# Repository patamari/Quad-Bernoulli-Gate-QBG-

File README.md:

This is a dual 4U adaptation of Mutable Instruments Branches. Hardware is cc-by-sa-3.0.

The only change component wise I had to make was to lower the values of the resistors for the -5V reference from 10K to 3.3K.

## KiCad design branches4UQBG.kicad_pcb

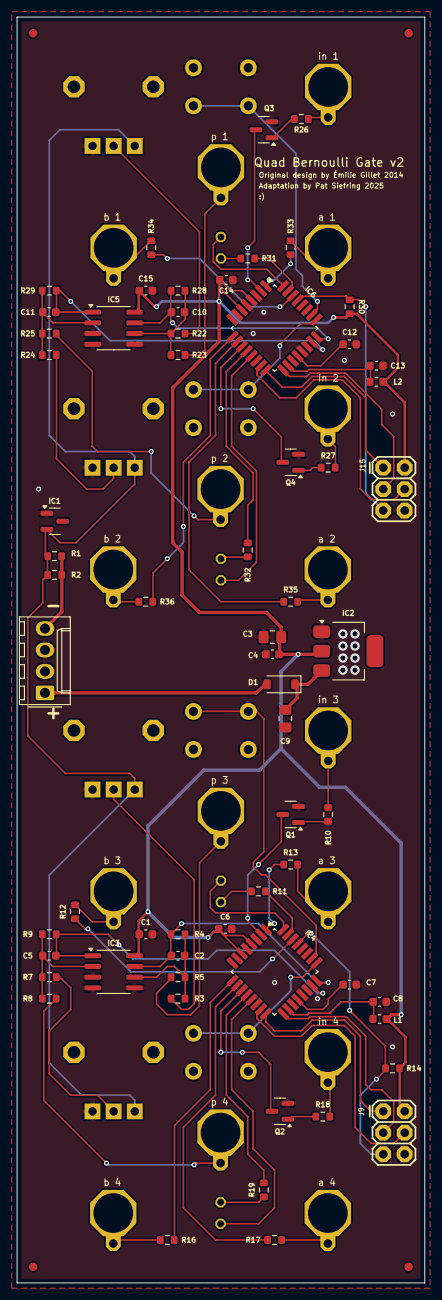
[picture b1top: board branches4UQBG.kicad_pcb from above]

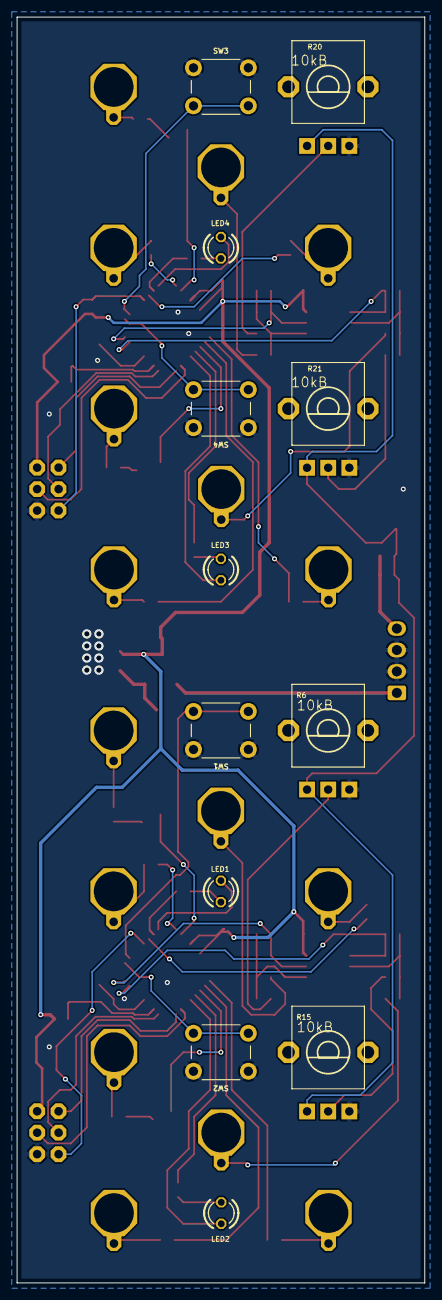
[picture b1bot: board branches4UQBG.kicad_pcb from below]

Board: 2 copper layers, 48.3 x 149.9 mm, 78 parts (12 on the bottom side), 61 nets.

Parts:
C1, C4, C6, C7, C8, C12, C13, C14, C15: 100n; C_0603_1608Metric
C2, C5, C10, C11: 1n; C_0603_1608Metric
C3, C9: 10uF; C_0805_2012Metric_Pad1.18x1.45mm_HandSolder
D1: 1N5819HW; D_SOD-123
F1, F2, F3, F4: FIDUCIAL1X2; FIDUCIAL-1X2
IC1: LM4040 5.0V; SOT-23
IC2: LM1117-5.0; SOT-223
IC3, IC5: MCP6002; SOIC-8_3.9x4.9mm_P1.27mm
IC4, IC6: ATMEGA88PA-AU; TQFP-32_7x7mm_P0.8mm
J9: 2X3
J15: AVR_SPI_PRG_6PTH; 2X3
L1: L_0603_1608Metric
L2: WE-CBF_0603; L_0603_1608Metric
LED1, LED2, LED3, LED4: WP937EGW; LED3MM
Q1, Q2, Q3, Q4: MMBT3904; SOT-23
R1, R2: 3.3K; R_0603_1608Metric
R3, R4, R5, R7, R8, R9, R10, R18, R22, R23, R24, R25, R26, R27, R28, R29: 100k; R_0603_1608Metric
R6, R15, R20, R21: 10kB; ALPS_POT_VERTICAL_PS
R11, R19, R31, R32: 220; R_0603_1608Metric
R12, R13, R16, R17, R33, R34, R35, R36: 1.0k; R_0603_1608Metric
R14, R30: 10k; R_0603_1608Metric
SW1, SW2: SW_PUSH_6mm_H4.3mm
SW3, SW4: TAC_SWITCHPTH; SW_PUSH_6mm_H4.3mm

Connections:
+5V: C1.1, C3.1, C4.1, C6.1, C14.1, C15.1, IC2.2, IC3.8, IC4.4, IC4.6, IC5.8, IC6.4 (VCC@1), IC6.6 (VCC@2), J9.2, J15.2, L1.1, L2.1, R14.2, R30.2
/AREF: C12.1, IC6.20 (AREF)
/IN1: IC6.2 (PD4(XCK/T0)), Q3.3
/IN2: IC6.11 (PD7(AIN1)), Q4.3
/MISO: IC6.16 (PB4(MISO)), J15.1
/MOSI: IC6.15 (PB3(MOSI/OC2)), J15.4
/OUT1_A: IC6.1 (PD3(INT1)), R33.1
/OUT1_B: IC6.30 (PD0(RXD)), R34.1
/OUT2_A: IC6.10 (PD6(AIN0)), R35.1
/OUT2_B: IC6.9 (PD5(T1)), R36.1
/P1_CV: C10.2, IC5.7 (OUT), IC6.24 (PC1(ADC1)), R28.2
/P2_CV: C11.2, IC5.1 (OUT), IC6.23 (PC0(ADC0)), R29.2
/RESET: IC6.29 (PC6(/RESET)), J15.5, R30.1
/SCK: IC6.17 (PB5(SCK)), J15.3
/SW1: IC6.26 (PC3(ADC3)), SW3.2
/SW2: IC6.25 (PC2(ADC2)), SW4.2
AREF: C7.1, IC4.20
GND: C1.2, C3.2, C4.2, C6.2, C7.2, C8.2, C9.2, C12.2, C13.2, C14.2, C15.2, IC1.1, IC2.1, IC3.3, IC3.4, IC3.5, IC4.3, IC4.5, IC4.21, IC5.3 (+IN), IC5.4, IC5.5 (+IN), IC6.3 (GND@1), IC6.5 (AGND), IC6.21 (GND@2), J9.6, J15.6, Q1.2, Q2.2, Q3.2, Q4.2, R6.P$1, R15.P$1, R20.P$1 (E), R21.P$1 (E), SW1.1, SW2.1, SW3.1, SW4.1
IN1: IC4.2, Q1.3
IN2: IC4.11, Q2.3
MISO: IC4.16, J9.1
MOSI: IC4.15, J9.4
unnamed: Q1.1, R10.1
unnamed: Q2.1, R18.1
unnamed: C5.1, IC3.2, R7.2, R8.2, R9.1
unnamed: R7.1, R15.P$2
unnamed: R3.1, R6.P$2
unnamed: IC4.31, R11.1
unnamed: LED1.A, R11.2
unnamed: IC4.32, LED1.K
unnamed: IC4.13, LED2.A
unnamed: LED2.K, R19.1
unnamed: IC4.12, R19.2
unnamed: C2.1, IC3.6, R3.2, R4.1, R5.2
unnamed: C8.1, IC4.18, L1.2
unnamed: C11.1, IC5.2 (-IN), R24.2, R25.2, R29.1
unnamed: C10.1, IC5.6 (-IN), R22.2, R23.2, R28.1
unnamed: C13.1, IC6.18 (AVCC), L2.2
unnamed: IC6.12 (PB0(ICP)), R32.2
unnamed: IC6.13 (PB1(OC1A)), LED3.A
unnamed: IC6.31 (PD1(TXD)), R31.1
unnamed: IC6.32 (PD2(INT0)), LED4.K (C)
unnamed: LED3.K (C), R32.1
unnamed: LED4.A, R31.2
unnamed: Q3.1, R26.1
unnamed: Q4.1, R27.1
unnamed: R20.P$2 (S), R22.1
unnamed: R21.P$2 (S), R24.1
OUT1_A: IC4.1, R13.1
OUT1_B: IC4.30, R12.1
OUT2_A: IC4.10, R17.1
OUT2_B: IC4.9, R16.1
P1_CV: C2.2, IC3.7, IC4.24, R4.2
P2_CV: C5.2, IC3.1, IC4.23, R9.2
REF_-5: IC1.2, R1.2, R2.2, R6.P$3, R15.P$3, R20.P$3 (A), R21.P$3 (A)
RESET: IC4.29, J9.5, R14.1
SCK: IC4.17, J9.3
SW1: IC4.26, SW1.2
SW2: IC4.25, SW2.2
VCC: C9.1, D1.1, IC2.3
VEE: R1.1, R2.1
